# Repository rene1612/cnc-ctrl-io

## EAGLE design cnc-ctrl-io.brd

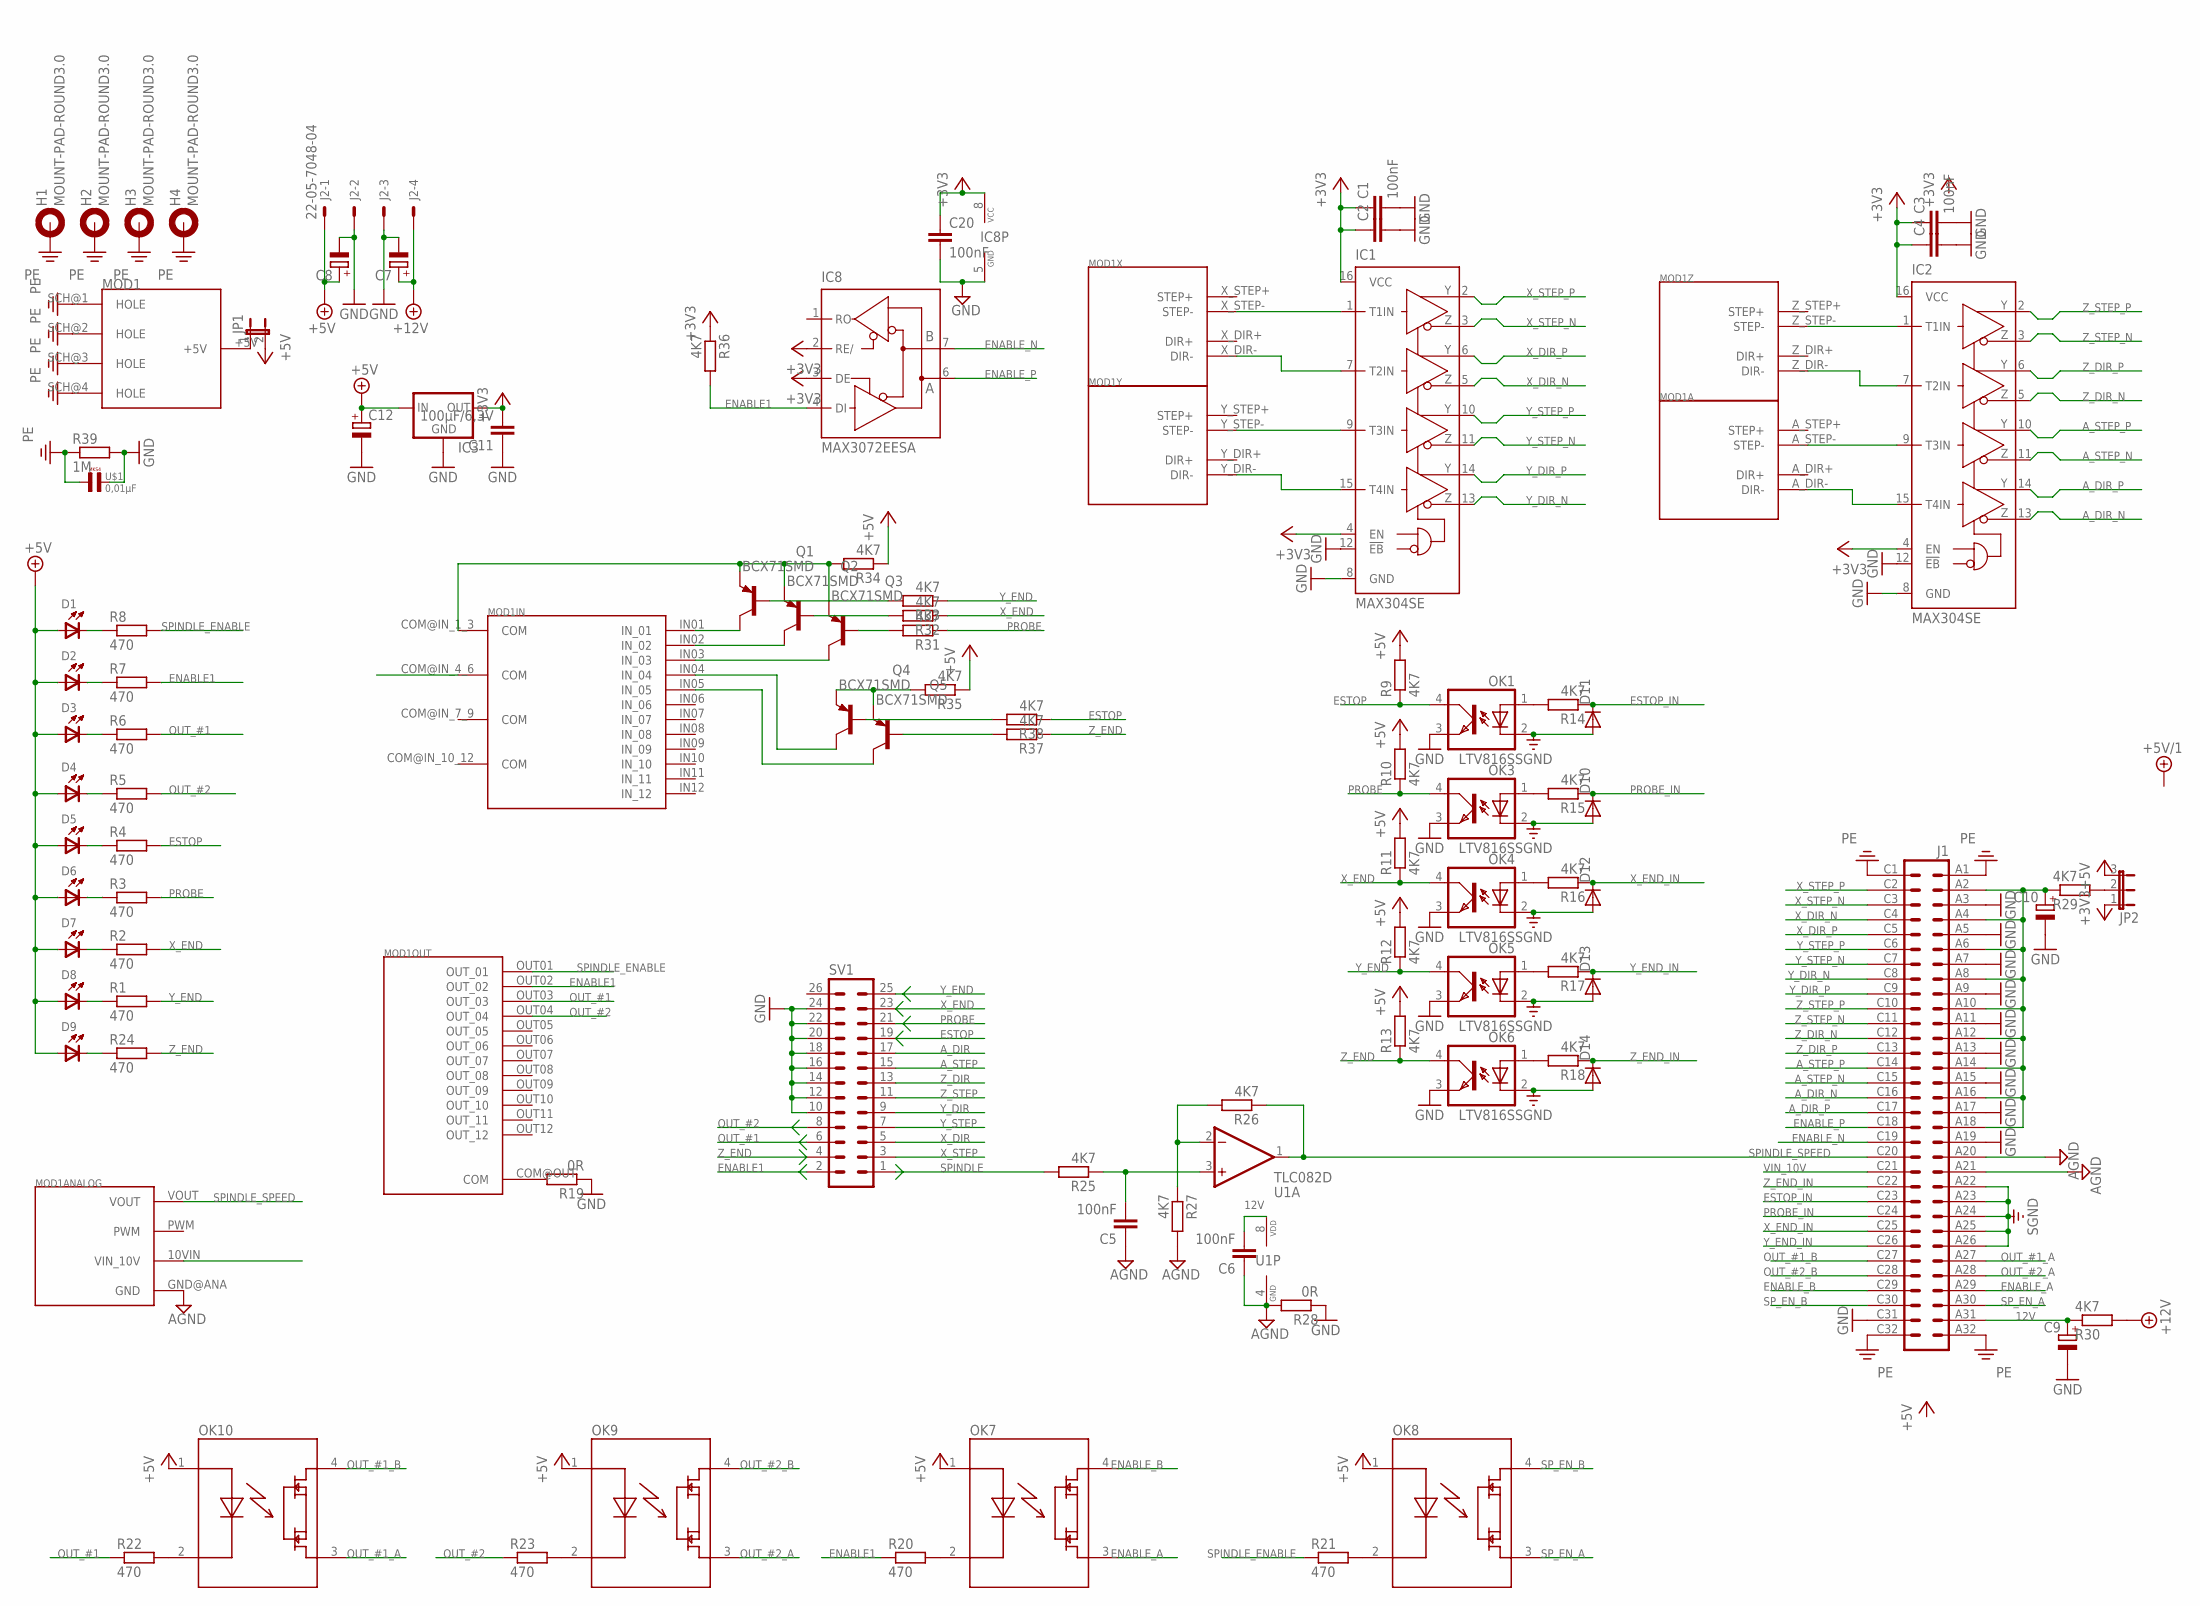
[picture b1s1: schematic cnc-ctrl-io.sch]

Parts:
C1, C3, C5, C6: 100nF; C0603K
C2, C4: C-EUC0603; C0603
C7, C8: CPOL-EUE3.5-8; E3,5-8
C9, C10, C12: CPOL-EUE2.5-5; E2,5-5
C11: 100µF/6,3V; C1206
C20: 100nF; C0603
D1, D2, D3, D4, D5, D6, D7, D8, D9: DL1; DL1N
D10, D11, D12, D13, D14: DIODE-SMB; SMB
H1, H2, H3, H4: MOUNT-PAD-ROUND3.0; 3,0-PAD
IC1, IC2: MAX304SE; SO16
IC3: LM1117TO252; TO252
IC8: MAX3072EESA; SO08
J1: VG64
J2: 22-05-7048-04; 7395-04
JP1: JP1E; JP1
JP2: JP2E; JP2
MOD1: DDLMV1
OK1, OK3, OK4, OK5, OK6: LTV816S; SMD4
OK7, OK8, OK9, OK10: AQY280; DIL4-SMD
Q1, Q2, Q3, Q4, Q5: BCX71SMD; SOT23
R1, R2, R3, R4, R5, R6, R7, R8, R20, R21, R22, R23, R24: 470; R0603
R9, R10, R11, R12, R13, R14, R15, R16, R17, R18, R25, R26, R27, R29, R30, R31, R32, R33, R34, R35, R36, R37, R38: 4K7; R0603
R19, R28: 0R; R0603
R39: 1M; R0603
SV1: ML26
U1: TLC082D; SO08
U$1: 0,01µF; R7K5B3

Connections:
12V: C6.2, C9.+, J1.A31, R30.1, U1.8 (VDD)
+3V3: C1.1, C2.1, C3.1, C4.1, C11.2, C20.1, IC1.4 (EN), IC1.16 (VCC), IC2.4 (EN), IC2.16 (VCC), IC3.3 (OUT), IC8.2 (RE/), IC8.3 (DE), IC8.8 (VCC), JP2.1, R36.1
+5V: C8.+, C12.+, D1.A, D2.A, D3.A, D4.A, D5.A, D6.A, D7.A, D8.A, D9.A, IC3.2 (IN), J2.1, JP1.2, JP2.3, OK7.1, OK8.1, OK9.1, OK10.1, R9.2, R10.2, R11.2, R12.2, R13.2, R34.1, R35.1
+12V: C7.+, J2.4, R30.2
AGND: C5.1, C6.1, J1.A20, J1.A21, MOD1.GND@ANA (GND), R27.2, R28.2, U1.4 (GND)
A_DIR: IC2.15 (T4IN), MOD1.A_DIR- (DIR-), SV1.17
A_DIR_N: IC2.13 (Z4), J1.C16
A_DIR_P: IC2.14 (Y4), J1.C17
A_STEP: IC2.9 (T3IN), MOD1.A_STEP- (STEP-), SV1.15
A_STEP_N: IC2.11 (Z3), J1.C15
A_STEP_P: IC2.10 (Y3), J1.C14
COM@IN_1_3: MOD1.COM@IN_1_3 (COM), Q1.2 (E), Q2.2 (E), Q3.2 (E), R34.2
COM@IN_4_6: MOD1.COM@IN_4_6 (COM), Q4.2 (E), Q5.2 (E), R35.2
ENABLE1: IC8.4 (DI), MOD1.OUT02 (OUT_02), R7.2, R20.1, R36.2, SV1.2
ENABLE_A: J1.A29, OK7.3
ENABLE_B: J1.C29, OK7.4
ENABLE_N: IC8.7 (B), J1.C19
ENABLE_P: IC8.6 (A), J1.C18
ESTOP: OK1.4 (COL), R4.2, R9.1, R38.1, SV1.19
ESTOP_IN: D11.C, J1.C23, R14.1
GND: C1.2, C2.2, C3.2, C4.2, C7.-, C8.-, C9.-, C10.-, C11.1, C12.-, C20.2, IC1.8 (GND), IC1.12 (!EB), IC2.8 (GND), IC2.12 (!EB), IC3.1 (GND), IC8.5 (GND), J1.A3, J1.A5, J1.A7, J1.A9, J1.A11, J1.A13, J1.A15, J1.A17, J1.A19, J1.C31, J2.2, J2.3, OK1.3 (EMIT), OK3.3 (EMIT), OK4.3 (EMIT), OK5.3 (EMIT), OK6.3 (EMIT), R19.1, R28.1, R39.2, SV1.10, SV1.12, SV1.14, SV1.16, SV1.18, SV1.20, SV1.22, SV1.24, U$1.2
IF_PWR: C10.+, J1.A2, J1.A4, J1.A6, J1.A8, J1.A10, J1.A12, J1.A14, J1.A16, J1.A18, R29.1
unnamed: OK9.2, R23.2
unnamed: D1.C, R8.1
unnamed: D2.C, R7.1
unnamed: D3.C, R6.1
unnamed: D4.C, R5.1
unnamed: D5.C, R4.1
unnamed: D6.C, R3.1
unnamed: D7.C, R2.1
unnamed: D8.C, R1.1
unnamed: OK1.1 (A), R14.2
unnamed: OK3.1 (A), R15.2
unnamed: OK4.1 (A), R16.2
unnamed: OK5.1 (A), R17.2
unnamed: OK6.1 (A), R18.2
unnamed: MOD1.COM@OUT (COM), R19.2
unnamed: OK7.2, R20.2
unnamed: OK8.2, R21.2
unnamed: OK10.2, R22.2
unnamed: D9.C, R24.1
unnamed: MOD1.IN01 (IN_01), Q1.3 (C)
unnamed: JP1.1, MOD1.+5V
unnamed: C5.2, R25.1, U1.3 (+IN)
unnamed: R26.2, R27.1, U1.2 (-IN)
unnamed: JP2.2, R29.2
unnamed: MOD1.IN02 (IN_02), Q2.3 (C)
unnamed: MOD1.IN03 (IN_03), Q3.3 (C)
unnamed: MOD1.IN04 (IN_04), Q4.3 (C)
unnamed: Q3.1 (B), R31.2
unnamed: Q2.1 (B), R32.2
unnamed: Q1.1 (B), R33.2
unnamed: MOD1.IN05 (IN_05), Q5.3 (C)
unnamed: Q5.1 (B), R37.2
unnamed: Q4.1 (B), R38.2
OUT_#1: MOD1.OUT03 (OUT_03), R6.2, R22.1, SV1.6
OUT_#1_A: J1.A27, OK10.3
OUT_#1_B: J1.C27, OK10.4
OUT_#2: MOD1.OUT04 (OUT_04), R5.2, R23.1, SV1.8
OUT_#2_A: J1.A28, OK9.3
OUT_#2_B: J1.C28, OK9.4
PE: H1.B3,0, H2.B3,0, H3.B3,0, H4.B3,0, J1.A1, J1.A32, J1.C1, J1.C32, MOD1.SCH@1 (HOLE), MOD1.SCH@2 (HOLE), MOD1.SCH@3 (HOLE), MOD1.SCH@4 (HOLE), R39.1, U$1.1
PROBE: OK3.4 (COL), R3.2, R10.1, R31.1, SV1.21
PROBE_IN: D10.C, J1.C24, R15.1
SGND: D10.A, D11.A, D12.A, D13.A, D14.A, J1.A22, J1.A23, J1.A24, J1.A25, J1.A26, OK1.2 (C), OK3.2 (C), OK4.2 (C), OK5.2 (C), OK6.2 (C)
SPINDLE: R25.2, SV1.1
SPINDLE_ENABLE: MOD1.OUT01 (OUT_01), R8.2, R21.1
SPINDLE_SPEED: J1.C20, MOD1.VOUT, R26.1, U1.1 (OUT)
SP_EN_A: J1.A30, OK8.3
SP_EN_B: J1.C30, OK8.4
VIN_10V: J1.C21
X_DIR: IC1.7 (T2IN), MOD1.X_DIR- (DIR-), SV1.5
X_DIR_N: IC1.5 (Z2), J1.C4
X_DIR_P: IC1.6 (Y2), J1.C5
X_END: OK4.4 (COL), R2.2, R11.1, R32.1, SV1.23
X_END_IN: D12.C, J1.C25, R16.1
X_STEP: IC1.1 (T1IN), MOD1.X_STEP- (STEP-), SV1.3
X_STEP_N: IC1.3 (Z1), J1.C3
X_STEP_P: IC1.2 (Y1), J1.C2
Y_DIR: IC1.15 (T4IN), MOD1.Y_DIR- (DIR-), SV1.9
Y_DIR_N: IC1.13 (Z4), J1.C8
Y_DIR_P: IC1.14 (Y4), J1.C9
Y_END: OK5.4 (COL), R1.2, R12.1, R33.1, SV1.25
Y_END_IN: D13.C, J1.C26, R17.1
Y_STEP: IC1.9 (T3IN), MOD1.Y_STEP- (STEP-), SV1.7
Y_STEP_N: IC1.11 (Z3), J1.C7
Y_STEP_P: IC1.10 (Y3), J1.C6
Z_DIR: IC2.7 (T2IN), MOD1.Z_DIR- (DIR-), SV1.13
Z_DIR_N: IC2.5 (Z2), J1.C12
Z_DIR_P: IC2.6 (Y2), J1.C13
Z_END: OK6.4 (COL), R13.1, R24.2, R37.1, SV1.4
Z_END_IN: D14.C, J1.C22, R18.1
Z_STEP: IC2.1 (T1IN), MOD1.Z_STEP- (STEP-), SV1.11
Z_STEP_N: IC2.3 (Z1), J1.C11
Z_STEP_P: IC2.2 (Y1), J1.C10

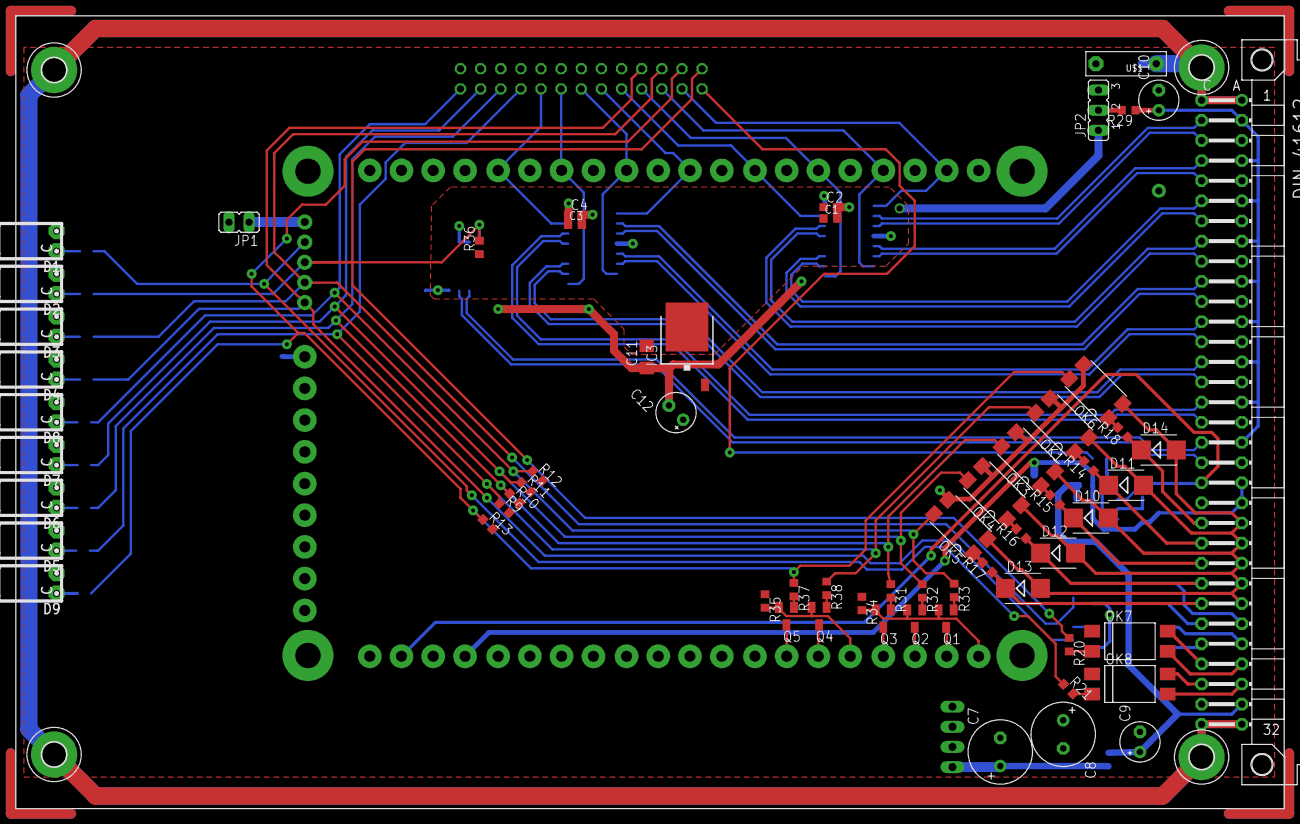
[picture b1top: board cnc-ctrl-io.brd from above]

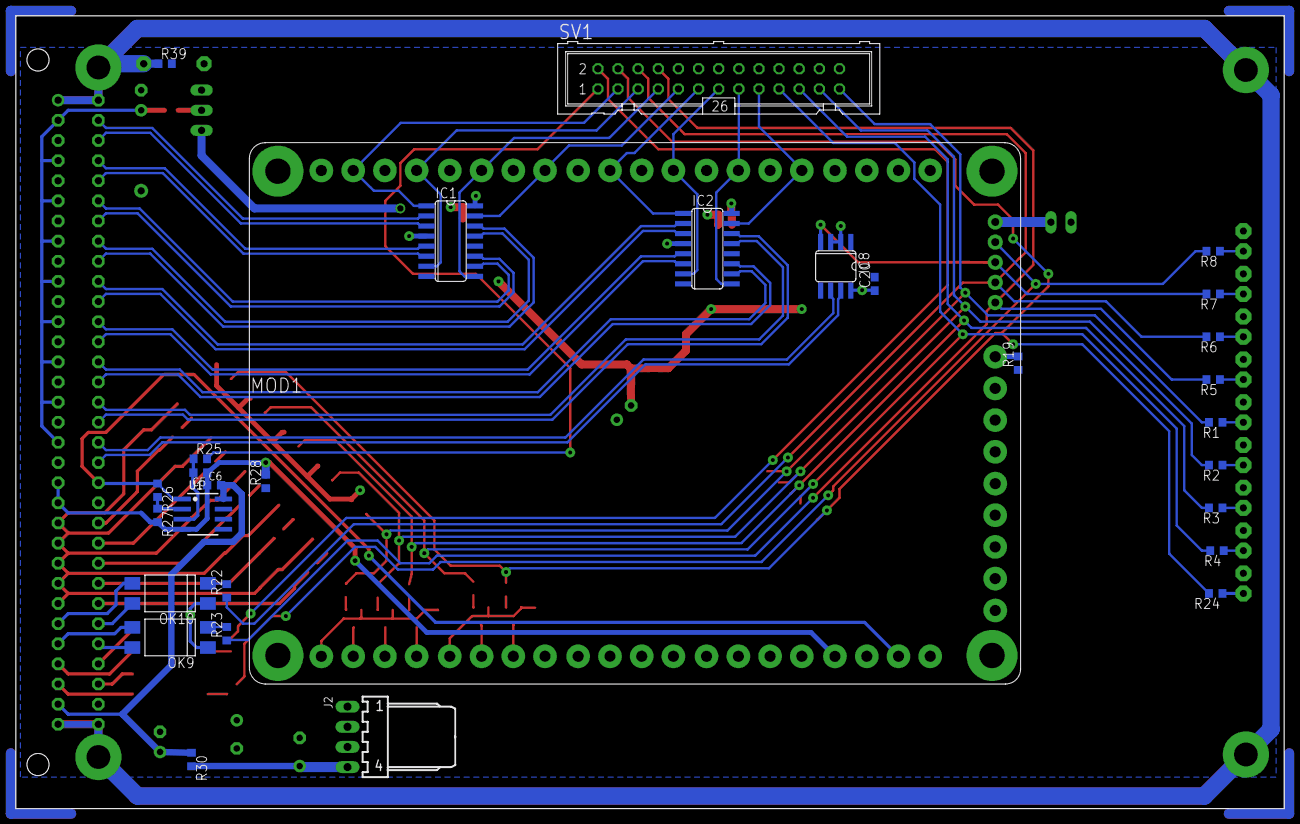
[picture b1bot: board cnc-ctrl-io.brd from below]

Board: 2 copper layers, 160.0 x 100.0 mm, 96 parts (30 on the bottom side), 94 nets.

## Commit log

2017-09-01 first commit, schematic ready
2017-09-04 DDLMV1-Inputs hinzugefügt @work
2017-09-07 Routing fertig @work
2017-09-08 lpt-connector verschoben, beschaltung für schirmung angepasst

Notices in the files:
parts and their libraries:
op-amp: Copyright (C) 2006 by Bob Starr
